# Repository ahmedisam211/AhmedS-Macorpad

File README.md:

# Ahmed's Macropad
This is a 10-key macropad with a rotary encoder and OLED display.
Its my Submission for Blueprint.

## Features
* 10x MX switches in a 2×5 matrix
* EC11 Rotary encoder — rotate for volume, push to mute
* 0.91" OLED display showing live volume level
* KMK firmware
* 3D printed case
* #KEEP_EYES_ON_SUDAN

## PCB
Made in KiCad. 2 layer board, just under 100×100mm.

### Schematic

## CAD 
Made in SolidWorks. Everything fits together using 
5x M3x16mm screws, screws and 5x M3x5x4mm heatset inserts.
5 printed parts: Top, Middle, Bottom, Base, Cover.

## Firmware
I used KMK for the firmware, each key has a seprate function, the rotary encoder controls the Vol level and the OLED displays the level.

## BOM
| Part | Quantity |
|---|---|
| Seeed XIAO RP2040 | 1 |
| MX Switches | 10 |
| 1N4148 Diodes | 10 |
| EC11 Rotary Encoder | 1 |
| 0.91" OLED Display | 1 |
| DSA Keycaps | 10 |
| M3x16mm Screws | 5 |
| M3x5x4mm Heatset Inserts | 5 |

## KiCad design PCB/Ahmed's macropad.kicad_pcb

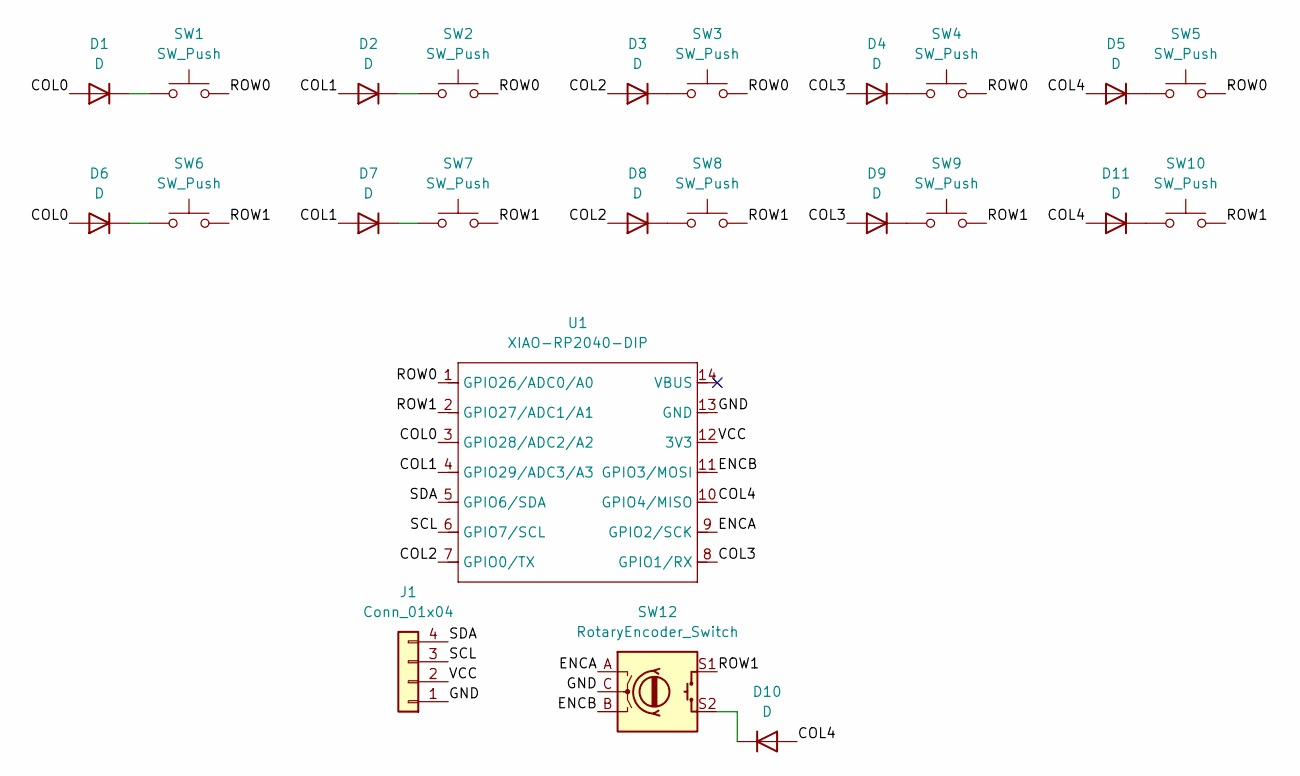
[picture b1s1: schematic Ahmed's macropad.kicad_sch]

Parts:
D1, D2, D3, D4, D5, D6, D7, D8, D9, D10, D11: D; D_DO-35_SOD27_P7.62mm_Horizontal
J1: Conn_01x04; PinHeader_1x04_P2.54mm_Vertical
SW1, SW2, SW3, SW4, SW5, SW6, SW7, SW8, SW9, SW10: SW_Push; SW_Cherry_MX_1.00u_PCB
SW12: RotaryEncoder_Switch; RotaryEncoder_Alps_EC11E-Switch_Vertical_H20mm_MountingHoles
U1: XIAO-RP2040-DIP

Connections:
/COL0: D1.2 (A), D6.2 (A), U1.3 (GPIO28/ADC2/A2)
/COL1: D2.2 (A), D7.2 (A), U1.4 (GPIO29/ADC3/A3)
/COL2: D3.2 (A), D8.2 (A), U1.7 (GPIO0/TX)
/COL3: D4.2 (A), D9.2 (A), U1.8 (GPIO1/RX)
/COL4: D5.2 (A), D10.2 (A), D11.2 (A), U1.10 (GPIO4/MISO)
/GND: J1.1 (GND), SW12.C, U1.13 (GND)
/ROW0: SW1.2, SW2.2, SW3.2, SW4.2, SW5.2, U1.1 (GPIO26/ADC0/A0)
/ROW1: SW6.2, SW7.2, SW8.2, SW9.2, SW10.2, SW12.S1, U1.2 (GPIO27/ADC1/A1)
/SCL: J1.3 (SCL), U1.6 (GPIO7/SCL)
/SDA: J1.4, U1.5 (GPIO6/SDA)
/VCC: J1.2 (VCC), U1.12 (3V3)
unnamed: D1.1 (K), SW1.1
unnamed: D2.1 (K), SW2.1
unnamed: D3.1 (K), SW3.1
unnamed: D4.1 (K), SW4.1
unnamed: D5.1 (K), SW5.1
unnamed: D6.1 (K), SW6.1
unnamed: D7.1 (K), SW7.1
unnamed: D8.1 (K), SW8.1
unnamed: D9.1 (K), SW9.1
unnamed: D10.1 (K), SW12.S2
unnamed: D11.1 (K), SW10.1
unnamed: SW12.A, U1.9 (GPIO2/SCK)
unnamed: SW12.B, U1.11 (GPIO3/MOSI)

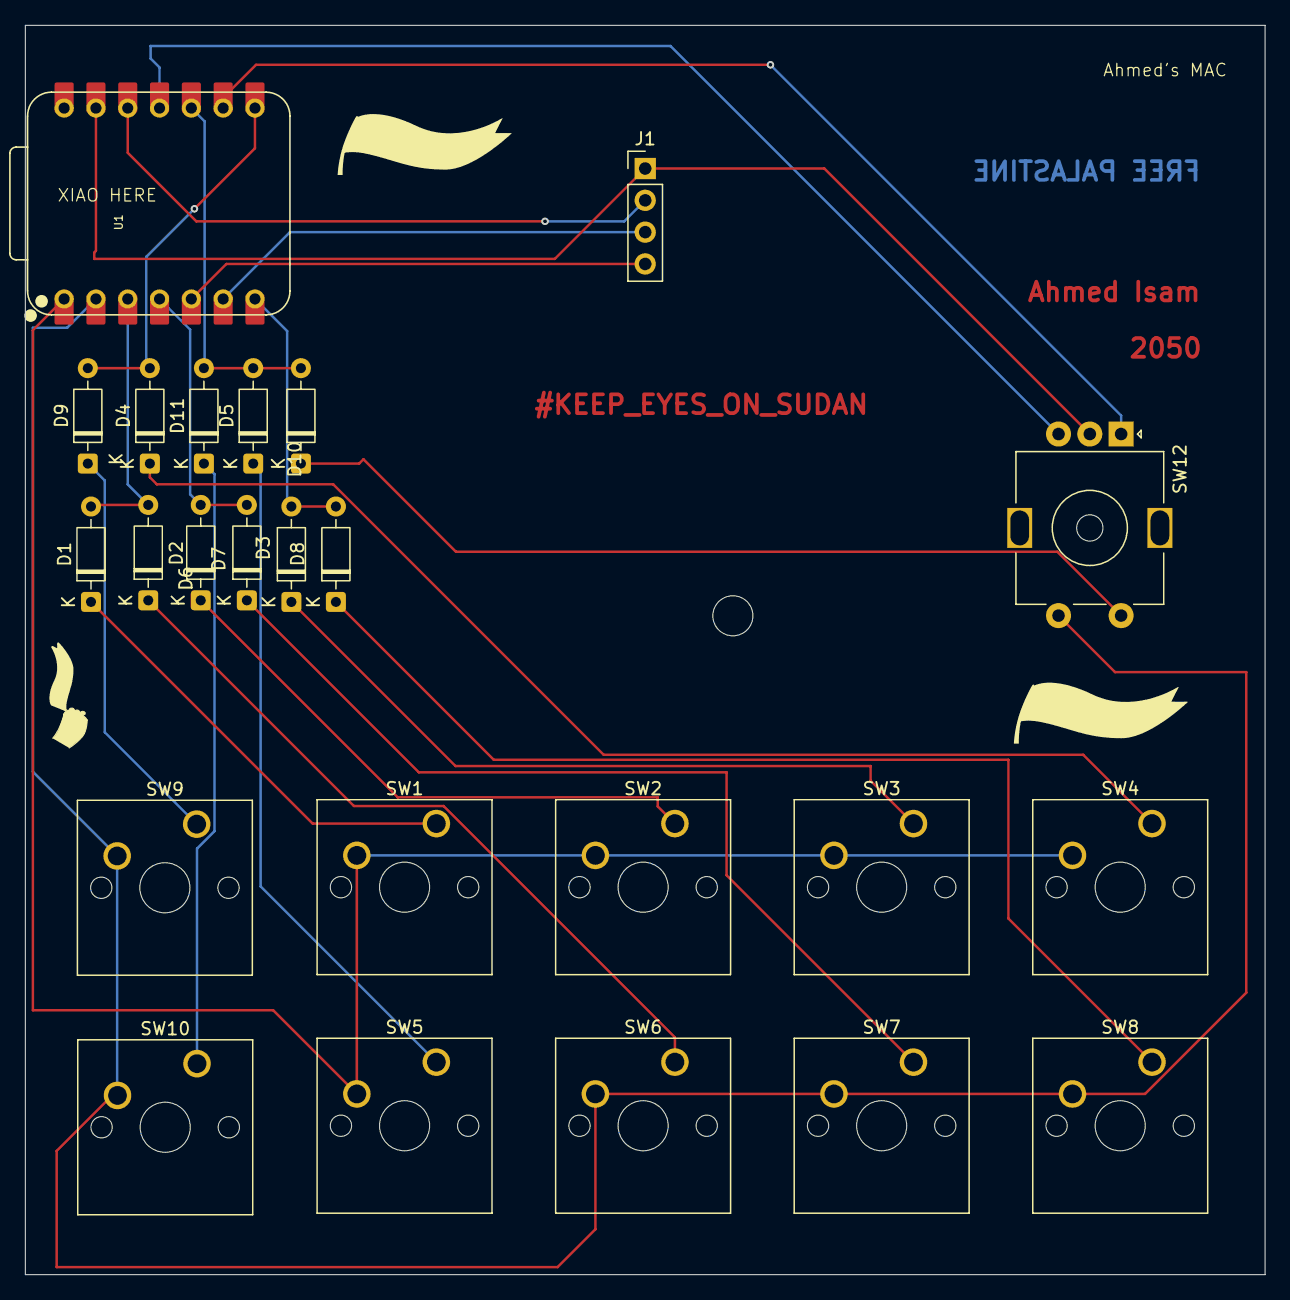
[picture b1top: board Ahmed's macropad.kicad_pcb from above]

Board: 2 copper layers, 99.0 x 99.8 mm, 24 parts (0 on the bottom side), 24 nets.

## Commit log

2026-03-29 Create README.md for Ahmed's Macropad project
    Added detailed project description, features, PCB, CAD, firmware, and BOM sections.
2026-03-29 Create assets
2026-03-29 Create Cad
